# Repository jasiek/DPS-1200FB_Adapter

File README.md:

Revision 1 is *slightly* buggy - the connectors don't quite have the pin spacing that was intended.

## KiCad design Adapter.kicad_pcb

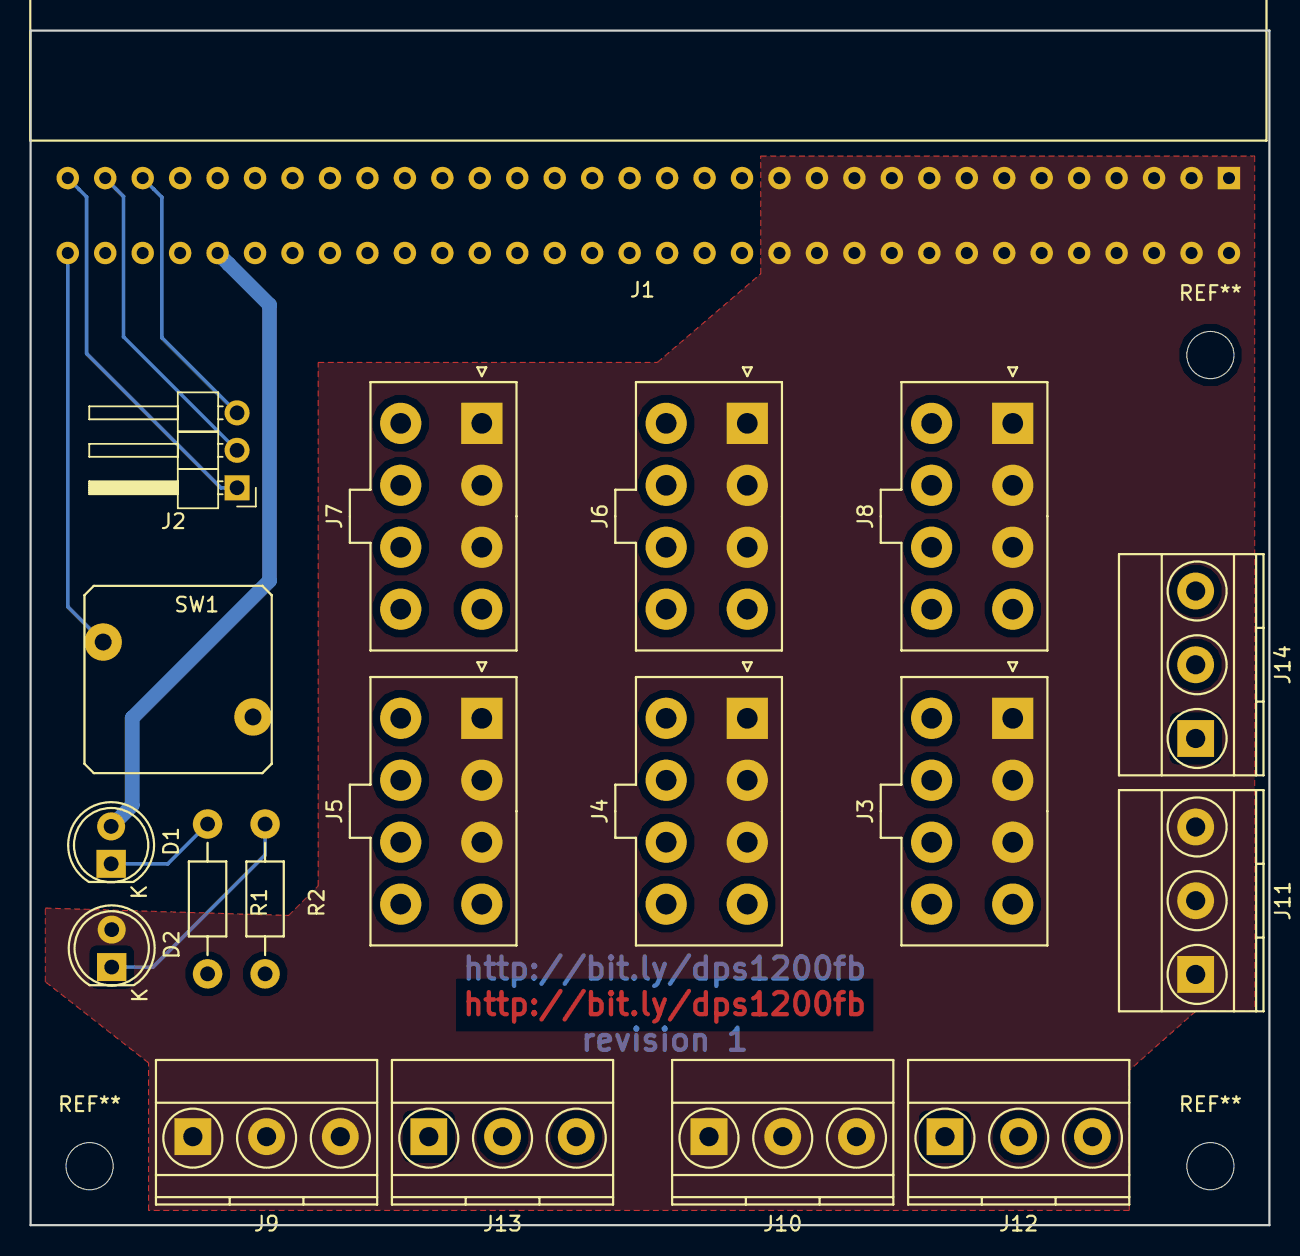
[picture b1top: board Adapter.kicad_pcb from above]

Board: 2 copper layers, 84.0 x 81.0 mm, 19 parts (0 on the bottom side), 9 nets.

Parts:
D1: LED_AMBER; LED-5MM
D2: LED_GREEN; LED-5MM
J1: PSU_CONNECTOR; COMMON_SLOT_PSU
J2: CONN_01X03; Pin_Header_Angled_1x03_Pitch2.54mm
J3, J4, J5, J6, J7, J8: PEG; Molex_MiniFit-JR-5556-08A_2x04x4.20mm_Straight
J9, J10, J11: 12V; TerminalBlock_Pheonix_MKDS1.5-3pol
J12, J13, J14: RTN; TerminalBlock_Pheonix_MKDS1.5-3pol
R1, R2: 560; Resistor_Horizontal_RM10mm
SW1: SW_SPST; SW_PUSH

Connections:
12V: D2.2, J1.1, J1.2, J1.3, J1.4, J1.5, J1.6, J1.7, J1.8, J1.9, J1.10, J1.11, J1.12, J1.13, J1.52, J1.53, J1.54, J1.55, J1.56, J1.57, J1.58, J1.59, J1.60, J1.61, J1.62, J1.63, J1.64, J3.1, J3.2, J3.3, J4.1, J4.2, J4.3, J5.1, J5.2, J5.3, J6.1, J6.2, J6.3, J7.1, J7.2, J7.3, J8.1, J8.2, J8.3, J9.1, J9.2, J9.3, J10.1, J10.2, J10.3, J11.1, J11.2, J11.3
12VSB: D1.2, J1.37
GND: J1.30, J2.3
unnamed: D1.1, R1.1
unnamed: D2.1, R2.1
PSON: J1.33, SW1.1
RTN: J1.14, J1.15, J1.16, J1.17, J1.18, J1.19, J1.20, J1.21, J1.22, J1.23, J1.24, J1.25, J1.26, J1.39, J1.40, J1.41, J1.42, J1.43, J1.44, J1.45, J1.46, J1.47, J1.48, J1.49, J1.50, J1.51, J3.4, J3.5, J3.6, J3.7, J3.8, J4.4, J4.5, J4.6, J4.7, J4.8, J5.4, J5.5, J5.6, J5.7, J5.8, J6.4, J6.5, J6.6, J6.7, J6.8, J7.4, J7.5, J7.6, J7.7, J7.8, J8.4, J8.5, J8.6, J8.7, J8.8, J12.1, J12.2, J12.3, J13.1, J13.2, J13.3, J14.1, J14.2, J14.3, R1.2, R2.2, SW1.2
SCL: J1.32, J2.1
SDA: J1.31, J2.2

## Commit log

2017-06-17 Initial commit.
2017-06-19 More elements.
2017-06-21 Generated netlist.
2017-06-21 Work in progress.
2017-06-21 Further layout work.
2017-06-22 Added PCB dimensions.
2017-07-11 Added a picture.
